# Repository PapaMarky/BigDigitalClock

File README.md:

# BigDigitalClock
Create a big 8 segment digital clock using LED strips for segments

## Shift Register Example
http://learn.pimoroni.com/tutorial/170pt-projects/the-shift-register-170pt

## Command Format ##

Q request

{'type': 'request', 'source':<handler thread>, 'msg': [...params...]}

{'type': 'response', 'source':<handler thread>, 'status': STATUS, 'detail': <None or "description">, 'msg': [...params...]}

{'type': 'notify', 'source': <None or handler thread>, 'msg': [...params...]}

STATUS: 'ok' | 'fail'

## Command Flow ##

ClockCLI
 |
 | client.send_message(msg)
\|/
ClockRequestHandler
 |
 | ClockServer.controller.handle(self, cur_thread, msg)
\|/
ClockControlThread
 |
 | self.display_q.put(request)
\|/
ClockWorksThread
 |
 | .run() -> .handle_job(job)
 |
 | self.control_q.put(results)
\|/
ClockControlThread.run()
 |
 |

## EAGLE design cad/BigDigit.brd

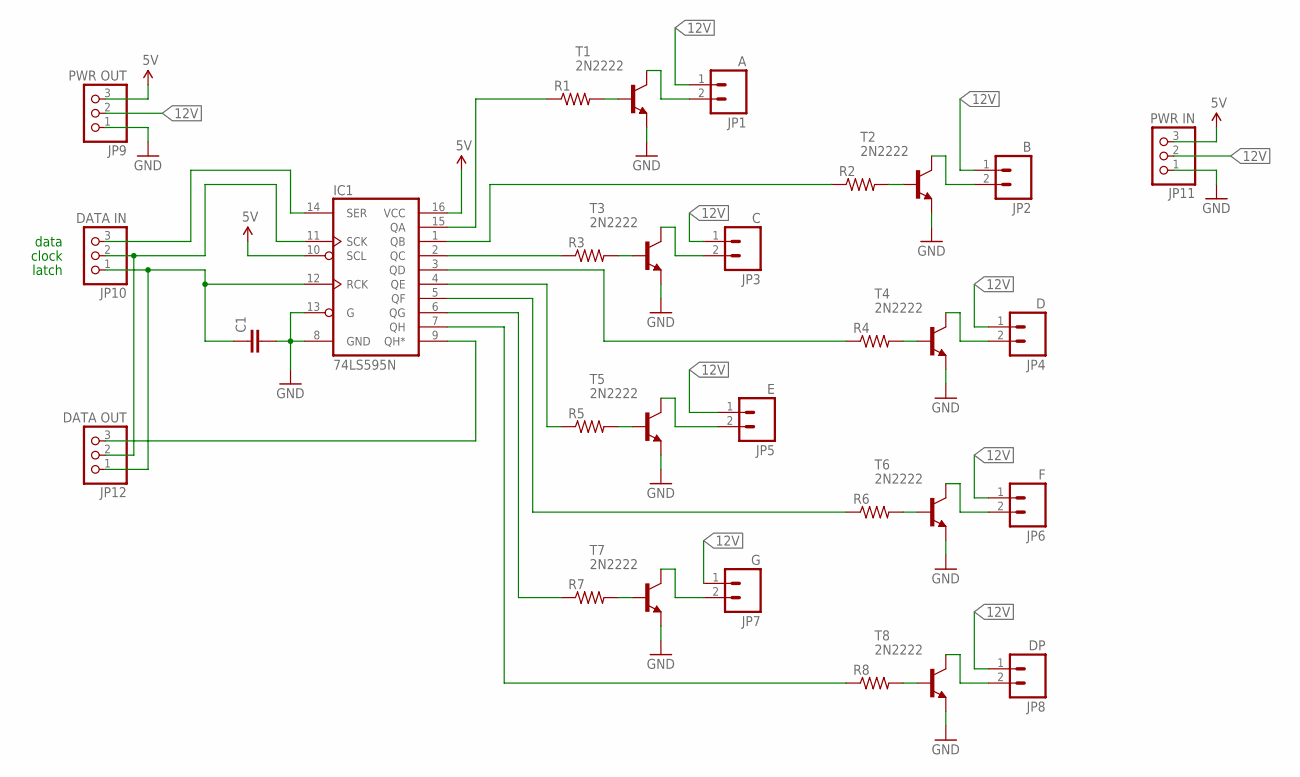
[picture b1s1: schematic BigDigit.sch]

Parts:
C1: 0.1UF-50V-20%(PTH)KIT-EZ; CAP-PTH-SMALL-KIT
IC1: 74LS595N; DIL16
JP1: A; 1X02
JP2: B; 1X02
JP3: C; 1X02
JP4: D; 1X02
JP5: E; 1X02
JP6: F; 1X02
JP7: G; 1X02
JP8: DP; 1X02
JP9: PWR OUT; 1X03-CLEANBIG
JP10: DATA IN; 1X03-CLEANBIG
JP11: PWR IN; 1X03-CLEANBIG
JP12: DATA OUT; 1X03-CLEANBIG
R1, R2, R3, R4, R5, R6, R7, R8: RESISTORPTH-1/4W-VERT; AXIAL-0.1
T1, T2, T3, T4, T5, T6, T7, T8: 2N2222; TO92-EBC-OVAL

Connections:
5V: IC1.10 (SCL), IC1.16 (VCC), JP9.3, JP11.3
12V: JP1.1, JP2.1, JP3.1, JP4.1, JP5.1, JP6.1, JP7.1, JP8.1, JP9.2, JP11.2
GND: C1.2, IC1.8 (GND), IC1.13 (G), JP9.1, JP11.1, T1.E, T2.E, T3.E, T4.E, T5.E, T6.E, T7.E, T8.E
unnamed: IC1.15 (QA), R1.P$1 (1)
unnamed: R1.P$2 (2), T1.B
unnamed: R5.P$2 (2), T5.B
unnamed: R3.P$2 (2), T3.B
unnamed: JP3.2, T3.C
unnamed: JP5.2, T5.C
unnamed: R7.P$2 (2), T7.B
unnamed: JP7.2, T7.C
unnamed: IC1.1 (QB), R2.P$1 (1)
unnamed: R2.P$2 (2), T2.B
unnamed: JP2.2, T2.C
unnamed: R4.P$2 (2), T4.B
unnamed: JP4.2, T4.C
unnamed: R6.P$2 (2), T6.B
unnamed: JP6.2, T6.C
unnamed: R8.P$2 (2), T8.B
unnamed: JP8.2, T8.C
unnamed: IC1.2 (QC), R3.P$1 (1)
unnamed: IC1.3 (QD), R4.P$1 (1)
unnamed: IC1.4 (QE), R5.P$1 (1)
unnamed: IC1.5 (QF), R6.P$1 (1)
unnamed: IC1.6 (QG), R7.P$1 (1)
unnamed: IC1.7 (QH), R8.P$1 (1)
unnamed: JP1.2, T1.C
unnamed: IC1.14 (SER), JP10.3
unnamed: IC1.11 (SCK), JP10.2, JP12.2
unnamed: C1.1, IC1.12 (RCK), JP10.1, JP12.1
unnamed: IC1.9 (QH*), JP12.3

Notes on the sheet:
data
clock
latch

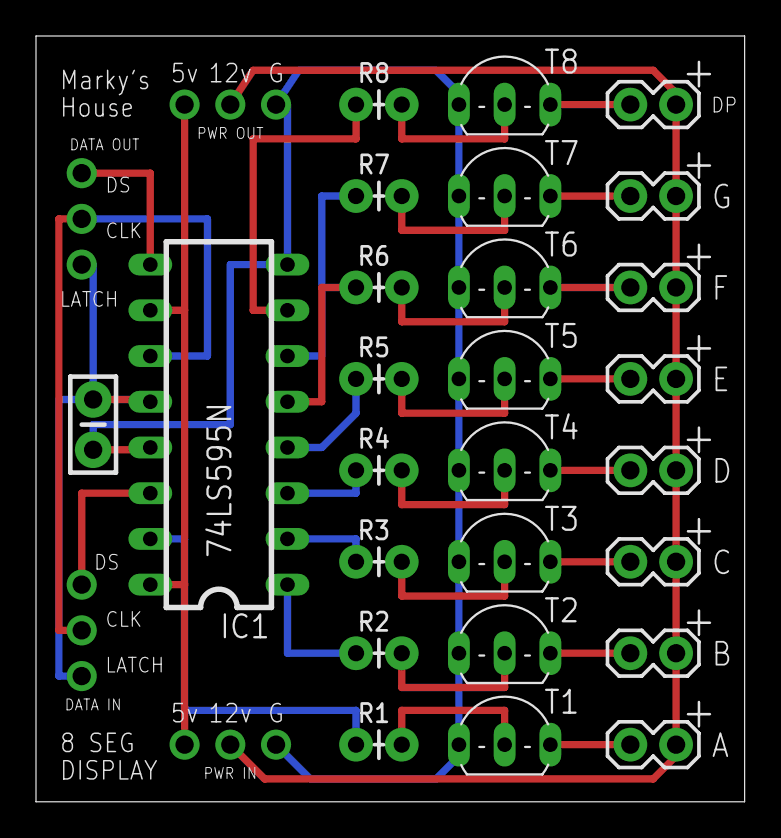
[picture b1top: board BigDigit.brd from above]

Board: 2 copper layers, 39.4 x 42.5 mm, 30 parts (0 on the bottom side), 31 nets.

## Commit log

2015-11-02 BDC: Create notes file to document pin assignment, etc
2015-11-05 BigClock: Add shifter sample that knows how to run the shift register.
2015-11-06 DigitalClock: move eagle files here from old repo
2015-11-06 DigitalClock: get digit definitions from old repo
    Reverse the bit order
2015-11-29 DigitalClock: Add test program DigitalClock
    Segments and DPs are working.
2015-12-22 DigitalClock: Implement basic clock functionality.
    It shows the time, but with no colons: HHMMSS
2015-12-23 DigitalClock: Start fleshing out architecture.
2016-01-24 DigitalClock: make service start at boot
2016-01-25 DigitalClock: Implement colons now that they are wired up.
2016-01-26 DigitalClock: Start work on 'ClockWorks' infrastructure.
2016-01-27 DigitalClock: Finish preliminary version of BigDisplay
    Also implemented support for looking up the bitmaps of digits in digit_defs.py
2016-01-27 DigitalClock: modify DigitalClock to use BigDisplay object
2016-01-27 DigitalClock: Start work on ClockControl thread
2016-01-28 DigitalClock: Start work on threaded implementation
2016-01-28 DigitalClock: CHECKPOINT work on threaded clock
2016-01-30 DigitalClock: get new software working with hardware
2016-01-30 DigitalClock: Add basics of brightness control. Add logging.
2016-02-01 DigitalClock: Basic framework for Client / server interface to clock control
2016-02-01 DigitalClock: More work connecting the chain of turtles.
2016-02-03 DigitalClock: Have most of Client - Server - controller - hardware chain working
2016-02-04 DigitalClock: more work on 'shutdown'
2016-02-05 DigitalClock: Got 'shutdown' command from client working end to end
2016-02-06 DigitalClock: Get 'shutdown' working end to end on Pi
    I guess sockets work diffently on Mac. :-(
2016-02-07 DigitalClock: more work getting shutdown to work on Pi
2016-02-07 DigitalClock: clean up
2016-02-07 DigitalClock: Add request handling mechanism to ClockWorksThread
2016-02-07 DigitalClock: Hook configuration into message handling flow
2016-02-08 DigitalClock: Fix ClockServer to shutdown without Exceptions.
2016-02-08 DigitalClock: Hook up BigDisplay to ClockWorksThread
2016-02-10 DigitalClock: Switch to pigpio library for better PWM
2016-06-02 DigitalClock: got digits and colons working
2016-06-05 DigitalClock: fix usage of global variable 'running'
2016-06-06 DigitalClock: Fix up service. Add service to launch pigpiod
2016-06-10 DigitalClock: add amplifier
2016-06-13 DigitalClock: Add 'auto' keyword for brightness. Start adding light sensor
2016-06-13 DigitalClock: Implement initialization from config file settings
2016-06-15 DigitalClock: 'brightness' returns new value. With no value returns current value.
2016-06-15 DigitalClock: implement initialization of lightsensor and autobrightness ranges
2016-06-16 DigitalClock: Hook up light sensor to auto-brightness
2016-06-16 DigitalClock: Add code to read temp/pressure/humidity sensor
2016-06-17 DigitalClock: fix typo
2016-06-19 DigitalClock: work on 'mode' / better execption handling (robustification)
2016-06-19 DigitalClock: use ClockCLI from ClockService to shutdown cleanly
2016-06-19 DigitalClock: Move time functionality into BigDisplay to support 'mode'
2016-06-20 Digital CLock: Redesigned (and documented) the Messages.
    Next I need to refactor the code.
2016-06-20 DigitalClock: move work from CLI into Client so it is reusable
2016-06-21 DigitalClock: basic infrastructure for 'get' requests.
    Fixed a bug that resulted in two responses
2016-06-22 DigitalClock: implement 'get' for mode and brightness.
2016-06-22 DigitalClock: implement 'set' for mode and brightness
2016-06-22 DigitalClock: clean up dead code. fix bug in set brightness error case
2016-06-23 DigitalClock: implemented timetemp mode
2016-06-23 DigitalClock: Add degrees character and use it in temp display
2016-06-23 DigitalClock: implement setting of 'temp scale'
2016-06-23 DigitalClock: implement 'get temp scale'
2016-06-23 DigitalClock: implement initialization of 'temp scale'
2016-06-25 DigitalClock: Implement 'clock zero_pad_hour'
2016-07-11 DigitalClock: Use third party 'bme280' python package instead of my port of Arduino verion
2016-07-11 DigitalClock: implement 'clock show_seconds', fix bugs in 'clock zero_pad_hour'
2016-07-14 DigitalClock: Start work on webserver
2016-07-24 DigitalClock: implement 'get all' to return entire config db
2016-07-24 DigitalClock: add clock config 'show_temp'
2016-07-24 DigitalClock: Deprecate timetemp mode
    timetemp is now achieved by setting 'clock show_temp' to True
2016-07-27 DigitalClock: Split JS out of HTML in prototype
2016-07-27 DigitalClock: Integrate prototype html into web app
2016-08-03 DigitalClock: allow setting of ipaddr and port for server connection
2016-08-03 DigitalClock: add support for remote server
2016-08-05 DigitalClock: fix issues with show_temp clock config * initialize was ignoring show_temp * ignoring seconds when show_seconds is False fixed flicker, but resulted in update problems.
2016-08-05 DigitalClock: fix indentation bug in 'get_light_sensor' that always returned None
2016-08-06 DigitalClock: get webapp communicating with clock server
2016-08-24 DigitalClock: Hook up web app to brightness
    It's way too slow responding. Tried turning down logging, did not help.

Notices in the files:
parts and their libraries:
SparkFun-DigitalIC: Licensing: CC v3.0 Share-Alike You are welcome to use this library for commercial purposes.
